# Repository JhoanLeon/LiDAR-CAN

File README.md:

# LiDAR-CAN BRDIGE MODULE - CASE STUDY Robot.com

This project was developed for a Robot.com case study. The entire project was developed using Git/GitHub version control so you can view all commits and incremental progress throughout the project's execution.

The requested deliverables for this case study are located in the OUTPUT folder.

For any questions, suggestions, or recommendations, please contact me by email: je.leon.e@outlook.com

Note: This project is available as a public GitHub repository at the following link: https://github.com/JhoanLeon/LiDAR-CAN

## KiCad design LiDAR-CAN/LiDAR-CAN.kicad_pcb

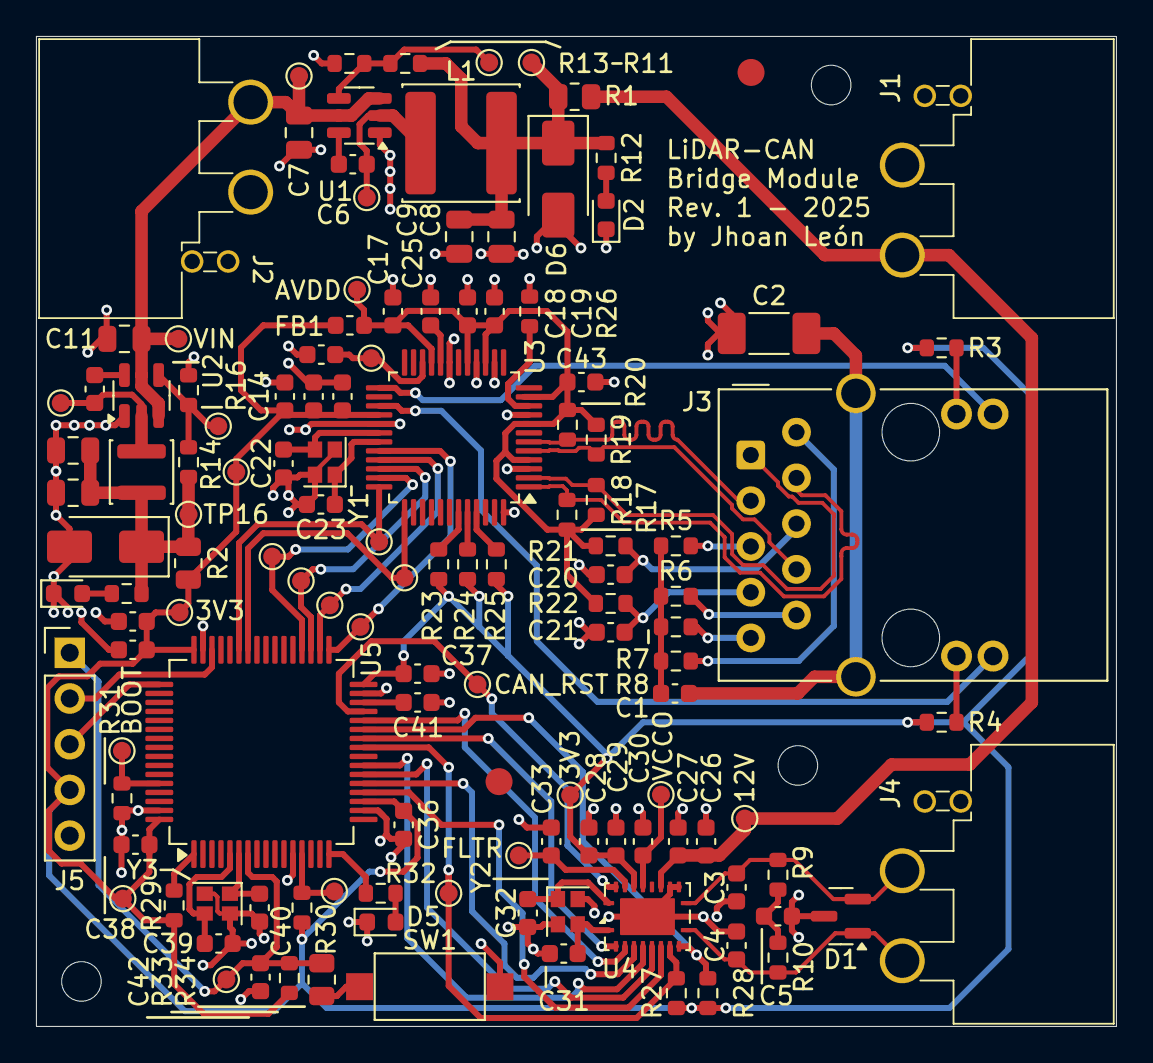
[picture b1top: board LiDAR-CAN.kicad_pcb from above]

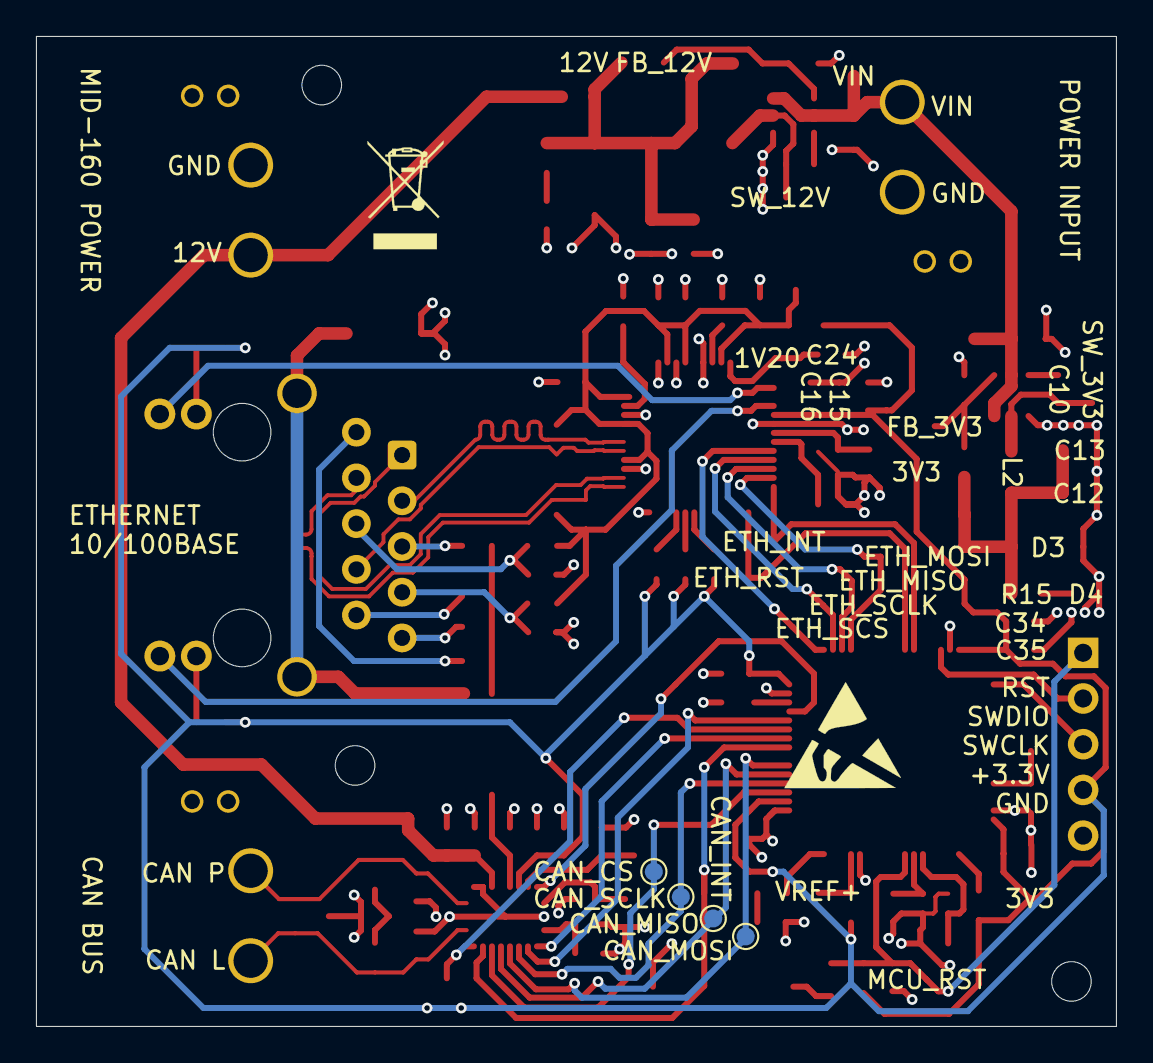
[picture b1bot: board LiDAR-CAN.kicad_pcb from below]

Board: 4 copper layers, 60.0 x 55.0 mm, 137 parts (4 on the bottom side), 73 nets.

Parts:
1V20, 3V3, 3V3#2, 3V3#3, 3V3#4, 12V, 12V#2: TestPoint; TestPoint_Pad_D1.0mm
AVDD: TestPoint; TestPoint_Pad_D1.0mm
BOOT: TestPoint; TestPoint_Pad_D1.0mm
C1, C5: 4.7nF; C_0603_1608Metric
C2: 1nF; C_1808_4520Metric
C3, C4: 100pF; C_0603_1608Metric
C6, C10, C15, C16, C18, C19, C27, C29, C35, C36, C37, C38, C43: 100nF; C_0603_1608Metric
C7, C11: 2.2uF; C_0805_2012Metric
C8, C9, C12, C13: 22uF; C_0805_2012Metric
C14, C17, C26, C28, C30, C34: 10uF; C_0603_1608Metric
C20, C21, C24, C42: 10nF; C_0603_1608Metric
C22, C23, C31, C32, C39, C40: 8pF; C_0603_1608Metric
C25, C41: 4.7uF; C_0603_1608Metric
C33: 330nF; C_0603_1608Metric
CAN_CS: TestPoint_Small; TestPoint_Pad_D1.0mm
CAN_INT: TestPoint; TestPoint_Pad_D1.0mm
CAN_MISO: TestPoint_Small; TestPoint_Pad_D1.0mm
CAN_MOSI: TestPoint_Small; TestPoint_Pad_D1.0mm
CAN_RST: TestPoint; TestPoint_Pad_D1.0mm
CAN_SCLK: TestPoint_Small; TestPoint_Pad_D1.0mm
D1: NUP2105L; SOT-23
D2, D4, D5: GREEN; LED_0603_1608Metric
D3: 5.1V; D_SMA
D6: 12V; D_SMA
ETH_INT: TestPoint; TestPoint_Pad_D1.0mm
ETH_MISO: TestPoint_Small; TestPoint_Pad_D1.0mm
ETH_MOSI: TestPoint_Small; TestPoint_Pad_D1.0mm
ETH_RST: TestPoint; TestPoint_Pad_D1.0mm
ETH_SCLK: TestPoint_Small; TestPoint_Pad_D1.0mm
ETH_SCS: TestPoint_Small; TestPoint_Pad_D1.0mm
FB1: MH1608-800Y; L_0603_1608Metric
FB_3V3, FB_12V: TestPoint; TestPoint_Pad_D1.0mm
FID1, FID2: Fiducial; Fiducial_1.5mm_Mask3mm
FLTR: TestPoint; TestPoint_Pad_D1.0mm
H1, H2, H3: MountingHole; MountingHole_2.2mm_M2
J1, J2, J4: XT30(2+2); XT30PW(2+2)-M.G.B
J3: G7LX-A88S7-BP-G/Y; RJ45_Kycon_G7LX-A88S7-BP-xx_Horizontal
J5: 61300511121; PinHeader_1x05_P2.54mm_Vertical
L1: 12uH; L_APV_ANR6020
L2: 5.6uH; L_APV_ANR3015
MCU_RST: TestPoint; TestPoint_Pad_D1.0mm
R1, R2: 0R; R_0805_2012Metric
R3, R4, R12, R15, R32: 300R; R_0603_1608Metric
R5, R6, R7, R8: 75R; R_0603_1608Metric
R9, R10: 59R; R_0603_1608Metric
R11, R14: 100k; R_0603_1608Metric
R13: 5.23k; R_0603_1608Metric
R16: 22.1k; R_0603_1608Metric
R17, R18, R19, R20: 49.9R; R_0603_1608Metric
R21, R22: 10R; R_0603_1608Metric
R23, R24, R25, R27, R28, R31, R33: 10k; R_0603_1608Metric
R26: 12.4k; R_0603_1608Metric
R29, R30: 0R; R_0603_1608Metric
R34: 22Ω; R_0805_2012Metric
SW1: RST; SW_SPST_CK_RS282G05A3
SW_3V3, SW_12V: TestPoint; TestPoint_Pad_D1.0mm
TP16: TestPoint; TestPoint_Pad_D1.0mm
U1, U2: LMR51430; SOT-23-6
U3: W5500; LQFP-48_7x7mm_P0.5mm
U4: TCAN4550RGY; Texas_RGY_R-PVQFN-N20_EP2.05x3.05mm
U5: STM32F401RBT6; LQFP-64_10x10mm_P0.5mm
VCCO: TestPoint; TestPoint_Pad_D1.0mm
VIN: TestPoint; TestPoint_Pad_D1.0mm
VIN#2: TestPoint; TestPoint_Pad_D1.0mm
VREF+: TestPoint; TestPoint_Pad_D1.0mm
Y1, Y3: 25MHz; Crystal_SMD_2016-4Pin_2.0x1.6mm
Y2: 40MHz; Crystal_SMD_2016-4Pin_2.0x1.6mm

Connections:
+3.3V: 3V3.1, 3V3#2.1, 3V3#3.1, 3V3#4.1, C14.1, C15.2, C16.2, C28.1, C29.2, C34.1, C35.2, C36.2, C37.2, C38.2, FB1.1, J5.4, R2.2, R3.1, R4.1, R23.1, R24.1, R25.1, R27.1, R28.1, R29.2, R30.2, R33.1, U3.28 (VDD), U4.17 (V_{IO}), U5.19 (VDD), U5.32 (VDD), U5.48 (VDD), U5.64 (VDD)
+12V: 12V.1, C26.1, C27.2, J1.1, R1.2, U4.14 (V_{SUP})
/CAN Interface/CAN+: C3.1, D1.2 (K), J4.2, R9.2, U4.11 (CANH)
/CAN Interface/CAN-: C4.1, D1.1 (K), J4.1, R10.2, U4.10 (CANL)
/CAN Interface/FLTR: C33.2, FLTR.1, U4.18 (FLTR)
/CAN Interface/GPIO1: U4.3 (GPO1), U5.28 (PB2)
/CAN Interface/GPIO2: R28.2, U4.9 (GPO2), U5.27 (PB1)
/CAN Interface/OSC1: C31.2, U4.1 (OSC1), Y2.3
/CAN Interface/OSC2: C32.2, U4.20 (OSC2), Y2.1
/CAN Interface/RST: CAN_RST.1, U4.19 (RST), U5.29 (PB10)
/CAN Interface/SCLK: CAN_SCLK.1, U4.4 (SCLK), U5.21 (PA5)
/CAN Interface/SDI: CAN_MOSI.1, U4.5 (SDI), U5.23 (PA7)
/CAN Interface/SDO: CAN_MISO.1, U4.6 (SDO), U5.22 (PA6)
/CAN Interface/VCCOUT: C30.1, U4.16 (V_{CCOUT}), VCCO.1
/CAN Interface/~CS: CAN_CS.1, U4.7 (~CS), U5.20 (PA4)
/CAN Interface/~INT: CAN_INT.1, R27.2, U4.8 (~INT), U5.25 (PC5)
/CAN Interface/~WKRQ: U4.2 (~WKRQ), U5.26 (PB0)
/LiDAR Interface/1V20: 1V20.1, C24.1, U3.22 (1V2O)
/LiDAR Interface/ACTLED: J3.13 (LEDG_K), U3.27 (ACTLED)
/LiDAR Interface/AVDD: AVDD.1, C17.1, C18.2, C19.2, C43.2, FB1.2, R17.2, R18.2, R19.2, R20.2, R21.1, R22.1, U3.4 (AVDD), U3.8 (AVDD), U3.11 (AVDD), U3.15 (AVDD), U3.17 (AVDD), U3.21 (AVDD)
/LiDAR Interface/EXRES1: R26.2, U3.10 (EXRES1)
/LiDAR Interface/LINKLED: J3.11 (LEDY_K), U3.25 (LINKLED)
/LiDAR Interface/MISO: ETH_MISO.1, U3.34 (MISO), U5.35 (PB14)
/LiDAR Interface/MOSI: ETH_MOSI.1, U3.35 (MOSI), U5.36 (PB15)
/LiDAR Interface/RCT: C21.1, J3.7 (RCT), R22.2
/LiDAR Interface/RXN: J3.6 (RD-), R19.1, U3.5 (RXN)
/LiDAR Interface/RXP: J3.3 (RD+), R20.1, U3.6 (RXP)
/LiDAR Interface/SCLK: ETH_SCLK.1, U3.33 (SCLK), U5.34 (PB13)
/LiDAR Interface/TCT: C20.1, J3.4 (TCT), R21.2
/LiDAR Interface/TOCAP: C25.1, U3.20 (TOCAP)
/LiDAR Interface/TXN: J3.2 (TD-), R17.1, U3.1 (TXN)
/LiDAR Interface/TXP: J3.1 (TD+), R18.1, U3.2 (TXP)
/LiDAR Interface/XI: C22.2, U3.30 (XI/CLKIN), Y1.3
/LiDAR Interface/XO: C23.2, U3.31 (XO), Y1.1
/LiDAR Interface/~INT: ETH_INT.1, U3.36 (~INT), U5.43 (PA10)
/LiDAR Interface/~RST: ETH_RST.1, U3.37 (~RST), U5.42 (PA9)
/LiDAR Interface/~SCS: ETH_SCS.1, U3.32 (~SCS), U5.33 (PB12)
/Microcontroller/BOOT0: BOOT.1, R31.1, U5.60 (BOOT0)
/Microcontroller/MCU_RST: C42.1, J5.1, MCU_RST.1, R33.2, R34.2, U5.7 (NRST)
/Microcontroller/OSC_IN: C39.2, U5.5 (PH0), Y3.3
/Microcontroller/OSC_OUT: C40.2, U5.6 (PH1), Y3.1
/Microcontroller/SWCLK: J5.3, U5.49 (PA14)
/Microcontroller/SWDIO: J5.2, U5.46 (PA13)
/Microcontroller/ULED: R32.1, U5.16 (PA2)
/Microcontroller/VREF+: R30.1, U5.13 (VREF+), VREF+.1
/Power Management/3.3VOUT: C12.1, C13.1, D3.1 (K), L2.2, R2.1, R14.1, R15.1, TP16.1
/Power Management/12VOUT: 12V#2.1, C8.1, C9.1, D6.1 (K), L1.2, R1.1, R11.1, R12.1
/Power Management/FB_3V3: FB_3V3.1, R14.2, R16.1, U2.4 (FB)
/Power Management/FB_12V: FB_12V.1, R11.2, R13.1, U1.4 (FB)
/Power Management/SW_3V3: C10.1, L2.1, SW_3V3.1, U2.2 (SW)
/Power Management/SW_12V: C6.1, L1.1, SW_12V.1, U1.2 (SW)
/Power Management/VIN: C7.1, C11.1, J2.1, U1.3 (VIN), U1.5 (EN), U2.3 (VIN), U2.5 (EN), VIN.1, VIN#2.1
CHASSIS_GND: C1.2, C2.2, J3.SH (SHIELD)
GND: C2.1, C3.2, C4.2, C5.2, C7.2, C8.2, C9.2, C11.2, C12.2, C13.2, C14.2, C15.1, C16.1, C17.2, C18.1, C19.1, C20.2, C21.2, C22.1, C23.1, C24.2, C25.2, C26.2, C27.1, C28.2, C29.1, C30.2, C31.1, C32.1, C33.1, C34.2, C35.1, C36.1, C37.1, C38.1, C39.1, C40.1, C41.2, C42.2, C43.1, D1.3 (A), D2.1 (K), D3.2 (A), D4.1 (K), D5.1 (K), D6.2 (A), J1.2, J2.2, J5.5, R13.2, R16.2, R26.1, R31.2, SW1.1, U1.1 (GND), U2.1 (GND), U3.3 (AGND), U3.9 (AGND), U3.14 (AGND), U3.16 (AGND), U3.19 (AGND), U3.29 (GND), U3.48 (AGND), U4.12 (WAKE), U4.13 (GND), U4.21 (GND), U5.12 (VSSA), U5.18 (VSS), U5.31 (VSS), U5.47 (VSS), U5.63 (VSS), Y1.2, Y1.4, Y2.2, Y2.4, Y3.2, Y3.4
unnamed: C1.1, R5.2, R6.2, R7.2, R8.2
unnamed: C5.1, R9.1, R10.1
unnamed: D2.2 (A), R12.2
unnamed: D4.2 (A), R15.2
unnamed: D5.2 (A), R32.2
unnamed: J3.14 (LEDG_A), R4.2
unnamed: J3.12 (LEDY_A), R3.2
unnamed: J3.5 (R1), R5.1
unnamed: J3.8 (R2), R6.1
unnamed: J3.10 (R3), R7.1
unnamed: J3.9 (R4), R8.1
unnamed: R34.1, SW1.2
unnamed: C6.2, U1.6 (CB)
unnamed: C10.2, U2.6 (CB)
unnamed: R25.2, U3.45 (PMODE0)
unnamed: R24.2, U3.44 (PMODE1)
unnamed: R23.2, U3.43 (PMODE2)
unnamed: R29.1, U5.1 (VBAT)
unnamed: C41.1, U5.30 (VCAP1)

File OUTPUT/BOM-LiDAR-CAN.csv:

"#","Reference","Qty","Value","Description","Manufacturer","MPN","DNP"
"1","C2","1","1nF","CAP CER 1808 1NF 2000V X7R 20%","KEMET","C1808C102MGRACAUTO",""
"2","C33","1","330nF","CAP CER 0.33UF 50V X7R 0603","KYOCERA AVX","KGM15BR71H334KT",""
"3","C1,C5","2","4.7nF","CAP CER 4700PF 50V X7R 0603","YAGEO","CC0603KRX7R9BB472",""
"4","C14,C17,C26,C28,C30,C34","6","10uF","CAP CER 10UF 25V X5R 0603","KYOCERA AVX","KGM15CR51E106KT",""
"5","C20,C21,C24,C42","4","10nF","CAP CER 10000PF 50V X7R 0603","YAGEO","CC0603KRX7R9BB103",""
"6","C22,C23,C31,C32,C39,C40","6","8pF","CAP CER 8PF 50V C0G/NPO 0603","YAGEO","CC0603DRNPO9BN8R0",""
"7","C25,C41","2","4.7uF","CAP CER 4.7UF 16V X5R 0603","YAGEO","CC0603KRX5R7BB475",""
"8","C3,C4","2","100pF","CAP CER 100PF 50V C0G/NPO 0603","YAGEO","CC0603JRNPO9BN101",""
"9","C6,C10,C15,C16,C18,C19,C27,C29,C35,C36,C37,C38,C43","13","100nF","CAP CER 0.1UF 50V X7R 0603","KYOCERA AVX","KGM15BR71H104KM",""
"10","C7,C11","2","2.2uF","CAP CER 2.2UF 50V X7R 0805","YAGEO","CC0805KKX7R9BB225",""
"11","C8,C9,C12,C13","4","22uF","CAP CER 22UF 25V X5R 0805","Samsung Electro-Mechanics","CL21A226MAYNNNE",""
"12","D1","1","NUP2105L","TVS DIODE 24VWM 44VC SOT233","onsemi","SZNUP2105LT1G",""
"13","D3","1","5.1V","DIODE ZENER 5.1V 1W SMA","Diodes Incorporated","SMAZ5V1-13-F",""
"14","D6","1","12V","DIODE ZENER 12V 1.5W SMA","onsemi","1SMA5927BT3G",""
"15","D2,D4,D5","3","GREEN","LED GREEN CLEAR CHIP SMD 0603","Lite-On Inc.","LTST-C190GKT",""
"16","FB1","1","MH1608-800Y","FERRITE BEAD 80 OHM 0603 1LN","Bourns Inc.","MH1608-800Y",""
"17","J3","1","G7LX-A88S7-BP-G/Y","1 Port RJ45 Through Hole 10/100 Base-T","Kycon, Inc.","G7LX-A88S7-BP-G/Y",""
"18","J5","1","61300511121","CONN HEADER VERT 5POS 2.54MM","Wurth Elektronik","61300511121",""
"19","J1,J2,J4","3","XT30(2+2)","Power connector XT30 PCB RA","Changzhou Amass Elec","XT30PW(2+2)-M.G.B",""
"20","L1","1","12uH","FIXED IND 12UH 2.2A 58 MOHM SMD","Abracon LLC","ASPI-6045S-120M-T",""
"21","L2","1","5.6uH","IND,3X3X1.3MM,5.6UH20%,1.8A,SHD","Bourns Inc.","SRN3015C-5R6M",""
"22","R13","1","5.23k","RES 5.23K OHM 1% 1/10W 0603","YAGEO","RC0603FR-075K23L",""
"23","R16","1","22.1k","RES 22.1K OHM 1% 1/10W 0603","YAGEO","RC0603FR-0722K1L",""
"24","R26","1","12.4k","RES 12.4K OHM 1% 1/10W 0603","YAGEO","RC0603FR-0712K4L",""
"25","R34","1","22R","RES 22 OHM 5% 1/8W 0805","YAGEO","RC0805JR-0722RL",""
"26","R1,R2","2","0R","RES 0 OHM JUMPER 0805","YAGEO","13-AC0805JR-130RLCT-ND",""
"27","R11,R14","2","100k","RES 100K OHM 1% 1/10W 0603","YAGEO","RT0603FRE13100KL",""
"28","R17,R18,R19,R20","4","49.9R","RES 49.9 OHM 1% 1/10W 0603","YAGEO","RC0603FR-0749R9L",""
"29","R21,R22","2","10R","RES SMD 10 OHM 5% 1/10W 0603","YAGEO","AC0603JR-0710RL",""
"30","R23,R24,R25,R27,R28,R31,R33","7","10k","RES 10K OHM 5% 1/10W 0603","YAGEO","RC0603JR-0710KL",""
"31","R29,R30","2","0R","RES 0 OHM JUMPER 1/10W 0603","YAGEO","RC0603JR-070RL",""
"32","R3,R4,R12,R15,R32","5","300R","RES 300 OHM 5% 1/10W 0603","YAGEO","RC0603JR-07300RL",""
"33","R5,R6,R7,R8","4","75R","RES SMD 75 OHM 5% 1/10W 0603","YAGEO","AC0603JR-0775RL",""
"34","R9,R10","2","59R","RES 59 OHM 1% 1/10W 0603","YAGEO","RC0603FR-0759RL",""
"35","SW1","1","RST","SWITCH TACTILE SPST-NO 0.05A 12V","C&K","RS-282G05A3-SM RT",""
"36","U3","1","W5500","IC CTLR 3-1 ETH TCP/IP 48LQFP","WIZnet","W5500",""
"37","U4","1","TCAN4550RGY","IC CAN FD CONTROLLER 20-VQFN","Texas Instruments","TCAN4550RGYRQ1",""
"38","U5","1","STM32F401RBT6","IC MCU 32BIT 128KB FLASH 64LQFP","STMicroelectronics","STM32F401RBT6",""
"39","U1,U2","2","LMR51430","IC REG BUCK ADJ 3A SOT23","Texas Instruments","LMR51430XDDCR",""
"40","Y2","1","40MHz","CRYSTAL 40.000 MHZ 6PF SMD","ECS Inc.","ECS-400-6-37Q-RES-TR",""
"41","Y1,Y3","2","25MHz","CRYSTAL 25 MHZ 6PF SMD","ECS Inc.","ECS-250-6-37B2-AGY-TR",""

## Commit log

2025-08-04 Initial commit
    Add KiCad project folder
2025-08-04 Add main schematic sheets
2025-08-04 Add main components in schematic sheets
2025-08-04 Add LiDAR Interface complete circuit
2025-08-04 Add RJ45 connector circuit
2025-08-04 Add testpoints to LiDAR interface circuit
2025-08-04 Add complete CAN Interface circuit
2025-08-04 Add external connector circuit
2025-08-04 Complete 70% of schematic design
2025-08-05 Add complete MCU circuit
2025-08-05 Add MCU connections in root sheet
2025-08-05 Add power management circuit
2025-08-05 Add power management connections in Root sheet
2025-08-05 Feature schematic revision 1
2025-08-05 Setup PCB stackup and routing
2025-08-05 Start placement of components
2025-08-05 Add CAN and MCU placement
2025-08-05 Update complete first placement
2025-08-05 Add CAN interface routing
2025-08-05 Add MCU routing
2025-08-05 Add 3.3V regulator routing
2025-08-05 Add 12V regulator routing
2025-08-05 Add Ethernet interface routing
2025-08-05 Add Ethernet connector routing
2025-08-05 Add SPI buses routing
2025-08-05 Complete routing and all nets
2025-08-05 Add new silkscreen annotation
2025-08-06 Complete silkscreen annotation
2025-08-06 Feature schematic revision 2
    Main changes related to connection wires for easy layout and minor components adjustments from Rev 1
2025-08-06 Feature layout revision 1
2025-08-06 Release v1.2.1
2025-08-06 Release LiDAR-CAN Bridge Module v1.2.1
2025-08-06 Add REAME file
